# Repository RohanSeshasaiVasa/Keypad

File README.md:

This is a KeyPad, made by Rohan Seshasai Vasa. This is a phase 2 of my button matrix game
I have used 5 switches to make this KeyPad. The switches used is Cherry MX. The reason I made this is that I had made an Arduino game.

Here is the game 
The game name is "Find a path". In this game for the first 5 seconds there will be some red(lava) dots will appear then disappear. After that green dots appear and we need to make a path between the 2 green dots without touching the lava dots(we need to memorize the positions).
So, in this game I used 4 x 4 LED and button matrix, I thought Button matrix has like 16 switches, and even more if I go there will be more like 64 keys. So instead of having that many keys, I will have 5 keys.

Switch 1 --> Up

Switch 2 --> Down

Switch 3 --> Left

Switch 4 --> Right

Switch 5 --> Ok / Start.

First we need to click Start button, then any one green dot glows, then you need to make a path between those 2 green dots using the switches.

These type of PCB's can be done on perforated boards for testing, so I took 5 normal switches and soldered it to the perf boards and it looks like this:

Backside:

Then I connected it to Arduino, changed the code to a KeyPad code and then tested, first I got some errors like mapping but resolved them.

Here is how the PCB actually looks:

Schematic

PCB

3D model of PCB

Front:

Back:

**BoM:**

| Item No. | Part Name        | Description              | Quantity | Unit | Total Cost(INR) | Links                                                                                                                                   |
|----------|------------------|--------------------------|----------|------|-----------------|-----------------------------------------------------------------------------------------------------------------------------------------|
| 1        | Cherry MX switch   | For pressing(clicky clicky)     | 1 (according to pcs in the link)        | pcs  | 482             | https://stackskb.com/store/cherry-mx-clear-switch-5-pin-pack-of-10/                          |
| 2        | Cherry MX switch Keycaps  | For casing of Switches     | 1 (according to pcs in the link)        | pcs  | 601             | https://www.amazon.in/gp/product/B0D9BRQNWK/ref=ewc_pr_img_2?smid=A4M88SXTNCUDD&psc=1                          | 
| 3        | Header Pins (2.54mm)| For attaching on the PCB         | 1        | pcs  | 135              | https://www.amazon.in/Plated-2-54mm-Header-Single-Straight/dp/B09HGTM3PS/ref=sr_1_5?sr=8-5    |
| 4        | PCB printing service | To order the PCB         | 5        | pcs  | 2510              | jlcpcb.com    |

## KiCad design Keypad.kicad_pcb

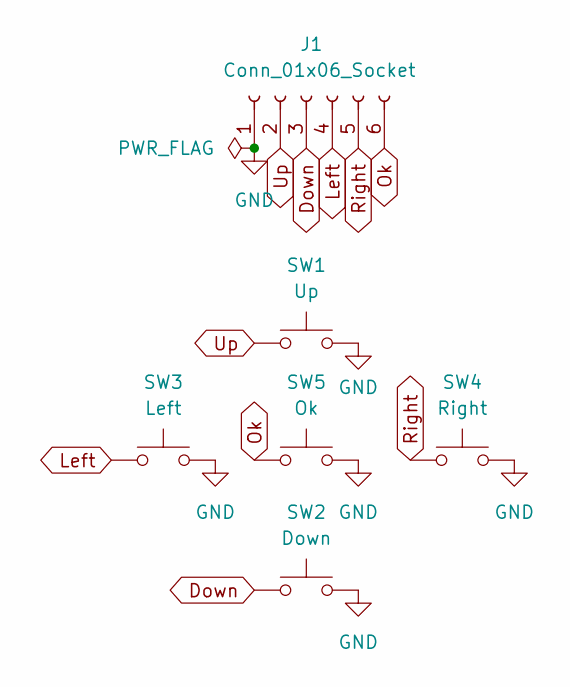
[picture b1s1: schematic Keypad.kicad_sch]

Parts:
J1: Conn_01x06_Socket; PinSocket_1x06_P2.54mm_Vertical
SW1: Up; SW_Cherry_MX_1.00u_PCB
SW2: Down; SW_Cherry_MX_1.00u_PCB
SW3: Left; SW_Cherry_MX_1.00u_PCB
SW4: Right; SW_Cherry_MX_1.00u_PCB
SW5: Ok; SW_Cherry_MX_1.00u_PCB

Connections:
Down: J1.3, SW2.1
GND: J1.1, SW1.2, SW2.2, SW3.2, SW4.2, SW5.2
Left: J1.4, SW3.1
Ok: J1.6, SW5.1
Right: J1.5, SW4.1
Up: J1.2, SW1.1

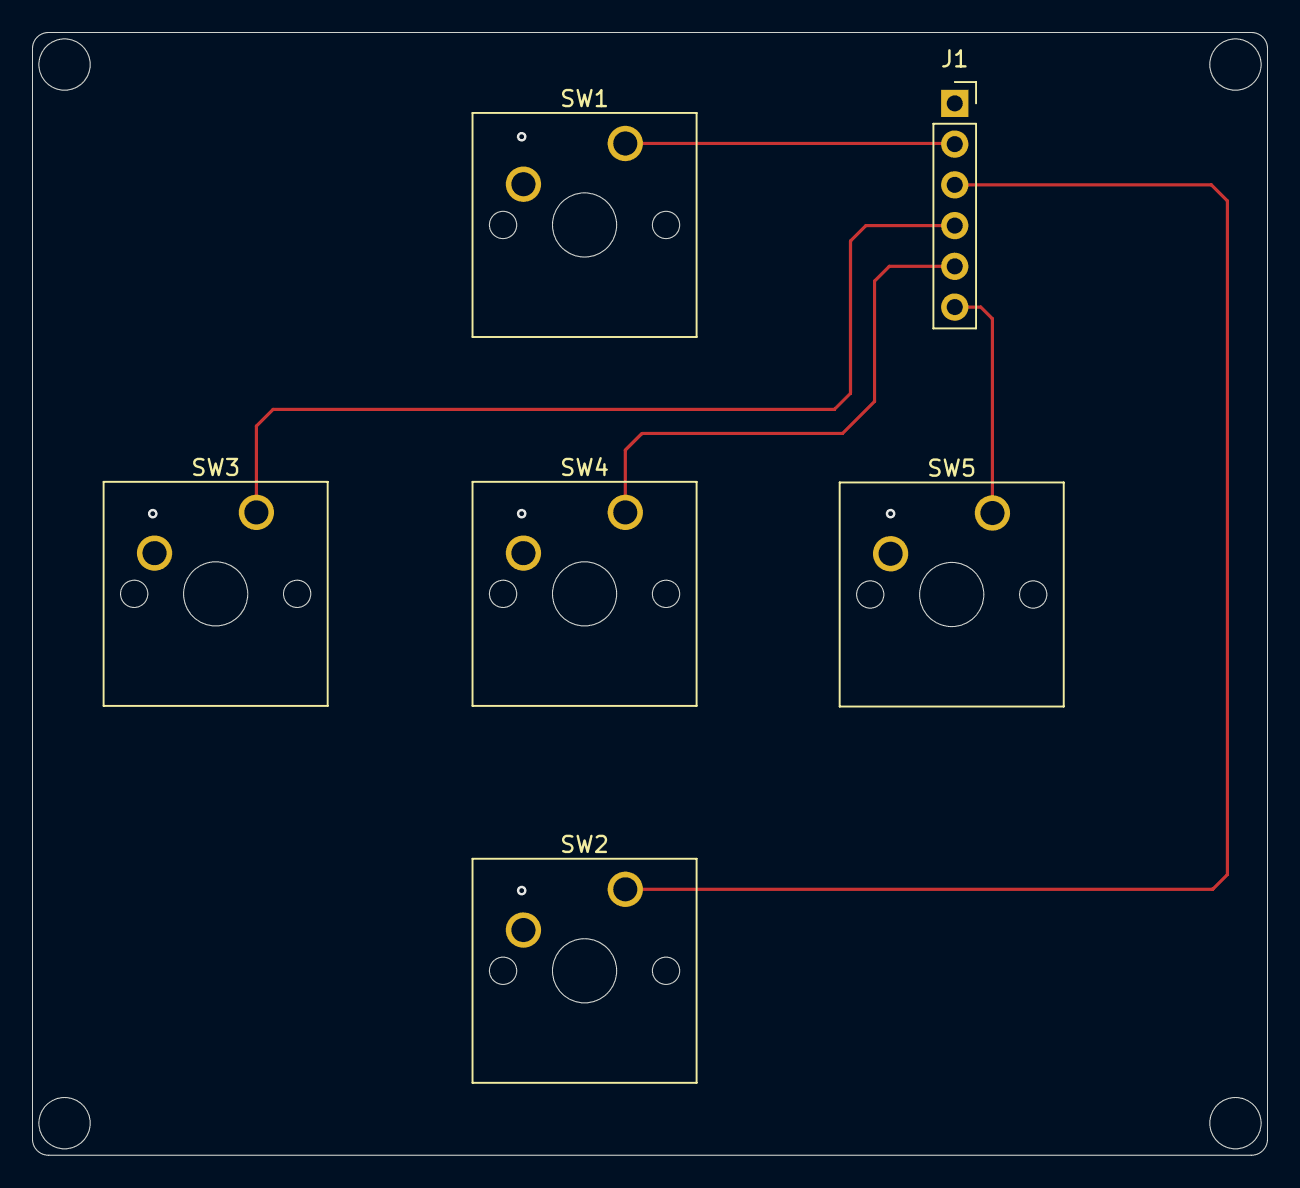
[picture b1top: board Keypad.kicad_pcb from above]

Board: 2 copper layers, 77.0 x 70.0 mm, 6 parts (0 on the bottom side), 6 nets.

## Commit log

2026-04-25 Initial Keypad project commit
2026-04-25 Add Keypad section to README
2026-04-25 Add journal entries for Day 1 of Arduino keypad project
    Documented the process of designing a keypad for an Arduino game, including schematic creation, PCB design, and CAD casing.
2026-04-25 Adjust hours and text for Day 1 session
    Updated hours spent on Day 1 (3rd session) from 4 to 2 hours and made minor adjustments to the text.
2026-04-30 Update README with KeyPad project details
    Added detailed description of the KeyPad project, including its purpose, game mechanics, and switch functions.
2026-04-30 Enhance README with game description and controls
    Added detailed explanation of game mechanics and controls.
2026-05-01 Added BoM files and also added the images
2026-05-01 Update Cherry MX switch cost and purchase link
    Updated the cost and link for Cherry MX switch.
2026-05-02 Updated links in the BoM
2026-05-09 Removed the lid
